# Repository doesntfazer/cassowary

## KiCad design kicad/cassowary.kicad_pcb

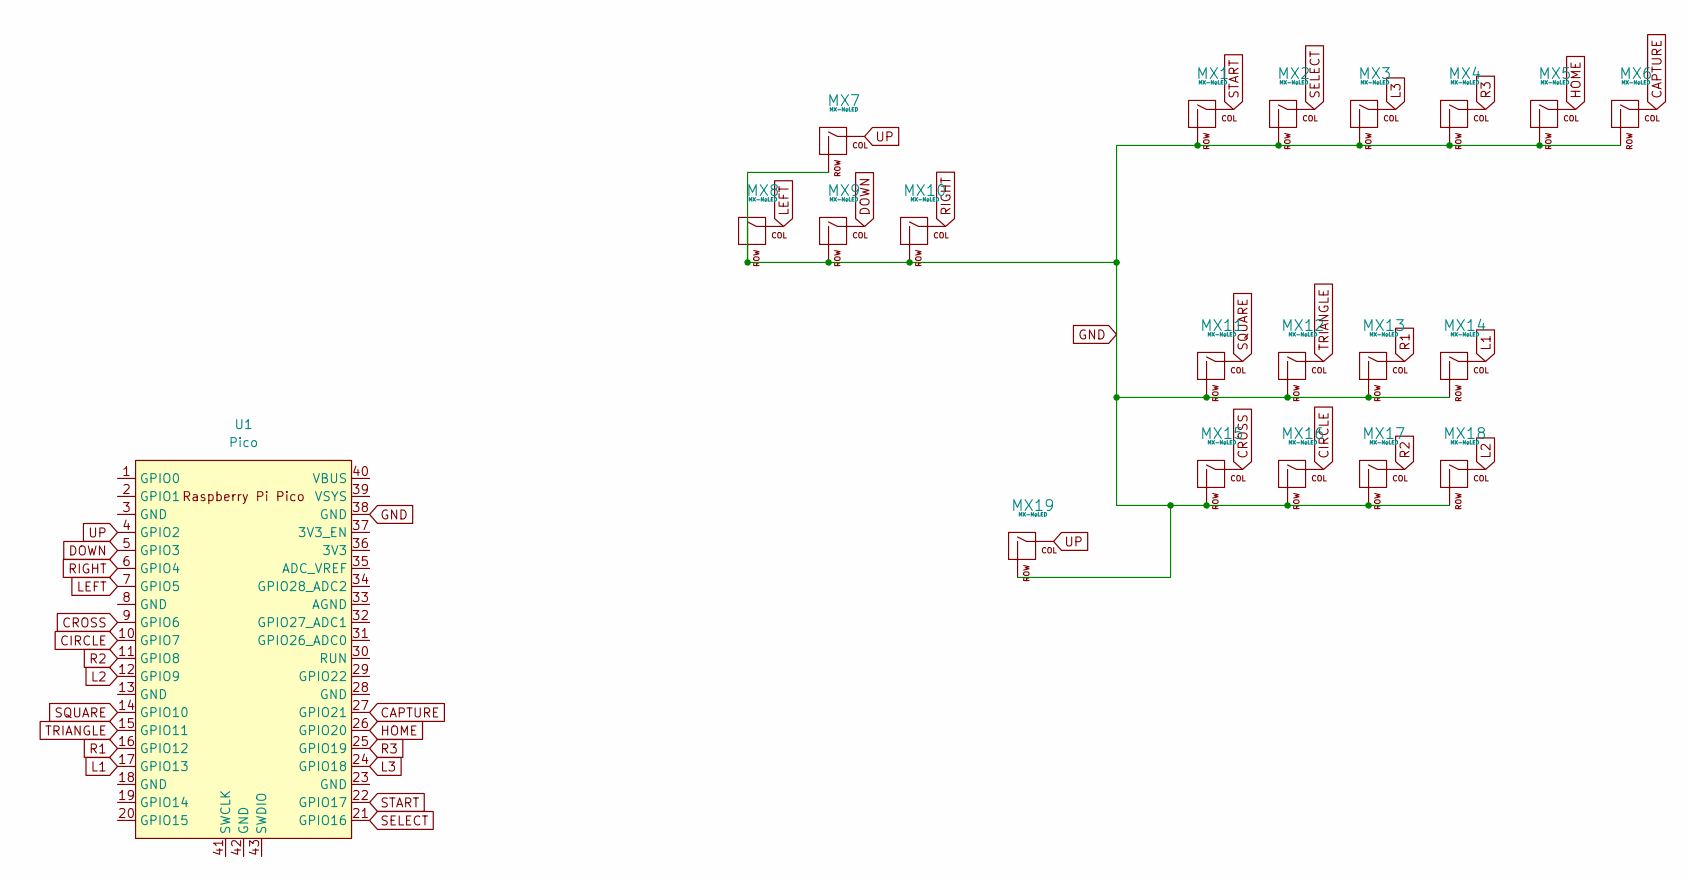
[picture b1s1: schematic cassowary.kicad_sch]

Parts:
MX1, MX2, MX3, MX4, MX5, MX6, MX7, MX8, MX9, MX10, MX11, MX12, MX13, MX14, MX15, MX16, MX17, MX18, MX19: MX-NoLED; SW_Cherry_MX_PCB_1.00u
U1: Pico; RPi_Pico_SMD_TH

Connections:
CAPTURE: MX6.1 (COL), U1.27 (GPIO21)
CIRCLE: MX16.1 (COL), U1.10 (GPIO7)
CROSS: MX15.1 (COL), U1.9 (GPIO6)
DOWN: MX9.1 (COL), U1.5 (GPIO3)
GND: MX1.2 (ROW), MX2.2 (ROW), MX3.2 (ROW), MX4.2 (ROW), MX5.2 (ROW), MX6.2 (ROW), MX7.2 (ROW), MX8.2 (ROW), MX9.2 (ROW), MX10.2 (ROW), MX11.2 (ROW), MX12.2 (ROW), MX13.2 (ROW), MX14.2 (ROW), MX15.2 (ROW), MX16.2 (ROW), MX17.2 (ROW), MX18.2 (ROW), MX19.2 (ROW), U1.38 (GND)
HOME: MX5.1 (COL), U1.26 (GPIO20)
L1: MX14.1 (COL), U1.17 (GPIO13)
L2: MX18.1 (COL), U1.12 (GPIO9)
L3: MX3.1 (COL), U1.24 (GPIO18)
LEFT: MX8.1 (COL), U1.7 (GPIO5)
R1: MX13.1 (COL), U1.16 (GPIO12)
R2: MX17.1 (COL), U1.11 (GPIO8)
R3: MX4.1 (COL), U1.25 (GPIO19)
RIGHT: MX10.1 (COL), U1.6 (GPIO4)
SELECT: MX2.1 (COL), U1.21 (GPIO16)
SQUARE: MX11.1 (COL), U1.14 (GPIO10)
START: MX1.1 (COL), U1.22 (GPIO17)
TRIANGLE: MX12.1 (COL), U1.15 (GPIO11)
UP: MX7.1 (COL), MX19.1 (COL), U1.4 (GPIO2)

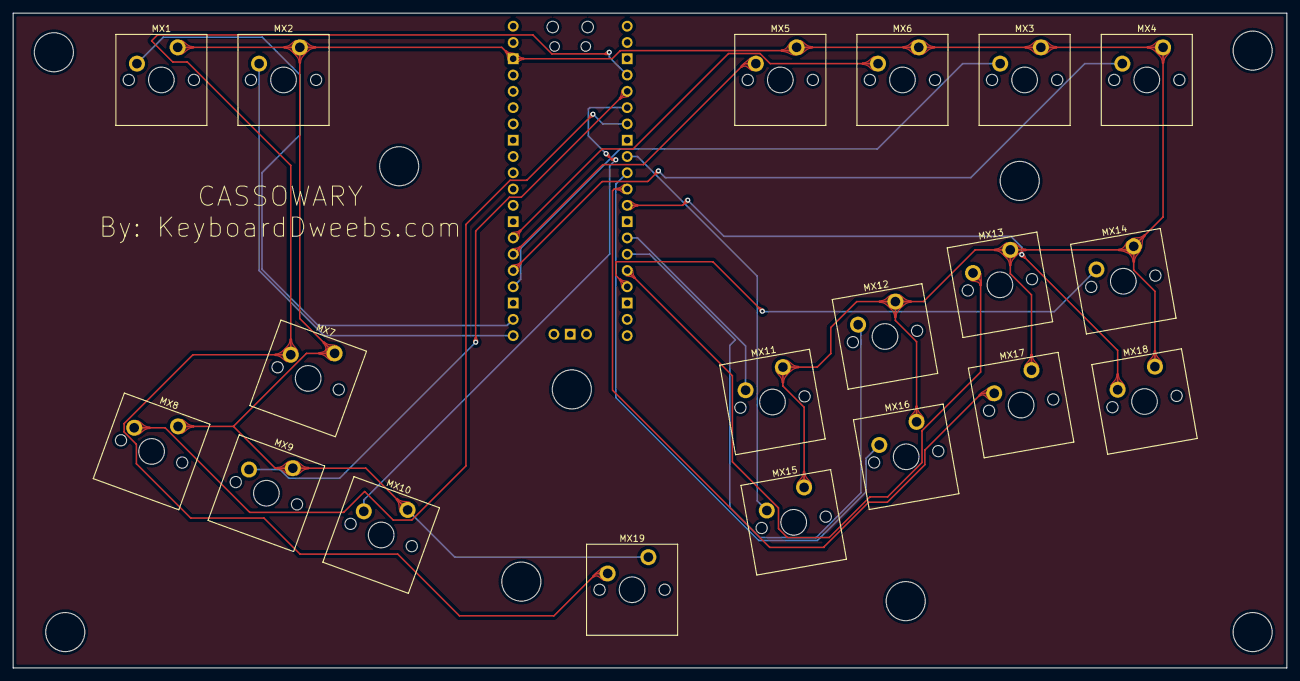
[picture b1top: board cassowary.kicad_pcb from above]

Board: 2 copper layers, 198.6 x 102.1 mm, 20 parts (1 on the bottom side), 19 nets.

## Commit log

2022-07-04 Kicad files
2022-07-04 removed backups
2022-07-04 removed folder
2022-07-04 add thumb key and fill
2022-07-04 gbr files
